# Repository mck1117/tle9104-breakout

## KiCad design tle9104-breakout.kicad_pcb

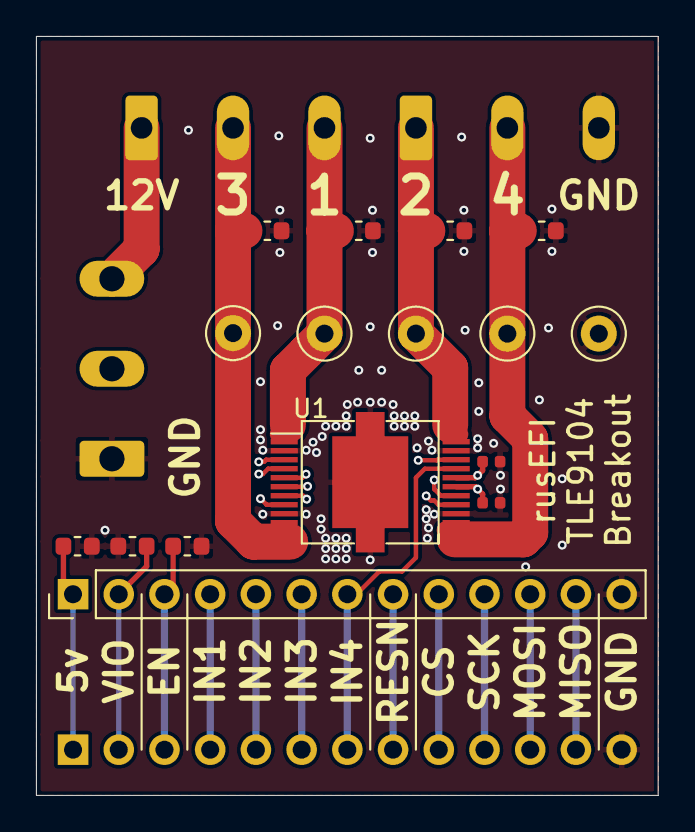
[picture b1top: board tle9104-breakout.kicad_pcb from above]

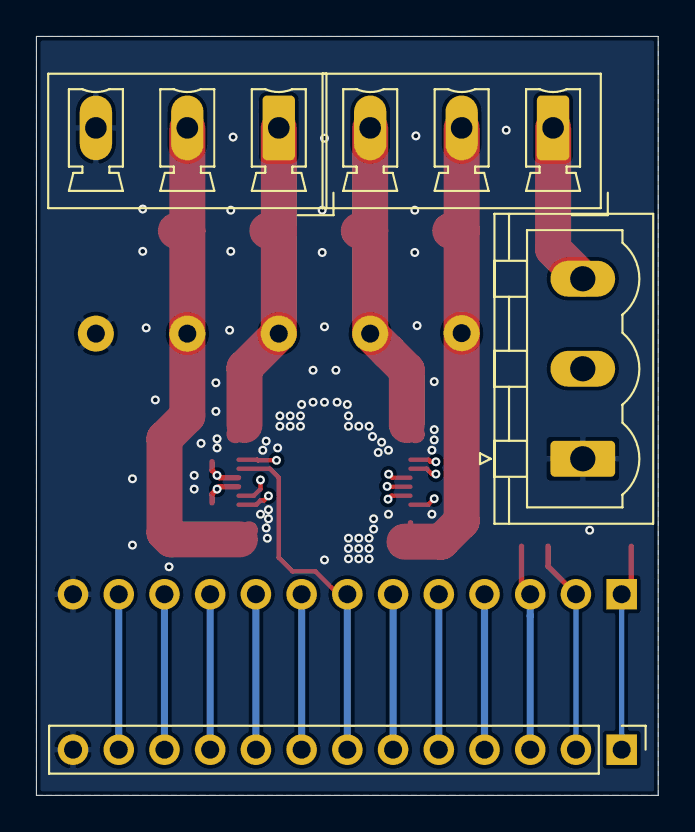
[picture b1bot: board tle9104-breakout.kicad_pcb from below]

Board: 4 copper layers, 34.5 x 42.2 mm, 20 parts (4 on the bottom side), 18 nets.

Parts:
C1, C2, C3, C4: 22n; C_0603_1608Metric
C5, C7: 1u; C_0603_1608Metric
C6, C8: 100n; C_0402_1005Metric
J1, J4: Conn_01x13; PinHeader_1x13_P2.54mm_Vertical
J2, J3: Conn_01x03_Female; PhoenixContact_MCV_1,5_3-G-5.08_1x03_P5.08mm_Vertical
J5: Conn_01x03_Female; PhoenixContact_MSTBVA_2,5_3-G_1x03_P5.00mm_Vertical
R1: 1k; R_0603_1608Metric
TP1, TP2, TP3, TP4, TP5: TestPoint; TestPoint_Loop_D2.50mm_Drill1.0mm
U1: TLE9104SH; PG-DSO-20-88

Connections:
+3V3: C7.1, C8.1, J1.2, J4.2, U1.15
+5V: C5.1, C6.1, J1.1, J4.1, U1.16
+12V: J2.1, J5.3
/CS: J1.9, J4.9, U1.7
/EN: J1.3, J4.3, R1.1, U1.14
/IN1: J1.4, J4.4, U1.3
/IN2: J1.5, J4.5, U1.18
/IN3: J1.6, J4.6, U1.4
/IN4: J1.7, J4.7, U1.17
/MISO: J1.12, J4.12, U1.5
/MOSI: J1.11, J4.11, U1.6
/OUT1: C3.1, J2.3, TP2.1, U1.1
/OUT2: C2.1, J3.1, TP3.1, U1.20
/OUT3: C4.1, J2.2, TP1.1, U1.10
/OUT4: C1.1, J3.2, TP4.1, U1.11
/RESN: J1.8, J4.8, U1.13
/SCK: J1.10, J4.10, U1.8
GND: C1.2, C2.2, C3.2, C4.2, C5.2, C6.2, C7.2, C8.2, J1.13, J3.3, J4.13, J5.1, R1.2, TP5.1, U1.2, U1.9, U1.12, U1.19, U1.21

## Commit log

2021-01-20 stub project
2021-01-20 module
2021-01-20 fix folder
2021-01-20 gitignore
2021-01-20 board
2021-01-20 update lib
2021-01-20 probably good enough
2021-01-20 export
